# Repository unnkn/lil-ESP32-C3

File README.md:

<!-- PROJECT LOGO -->
<br />
<div align="center">

  <h3 align="center">Little ESP32 C3 Charger with wireless capabilities</h3>

  <p align="center">
    Here you can find all my project files.
    <br />
    <a href="https://github.com/Ans1S/lil-ESP32-C3"><strong>Explore the docs »</strong></a>
    <br />
    <br />
    <a href="https://github.com/Ans1S/lil-ESP32-C3/issues">Report Bug</a>
  </p>
</div>

## PCB Version 1: Advanced Wireless Communication and Power Management
<div align="center">

</div>

<div align="center">
  
</div>

<br />
<br />

The objective of this project is to develop a compact ESP32-C3 board with integrated Wi-Fi and Bluetooth capabilities. One of the standout features of this board is its ability to charge a LiPo battery (3.7V) while managing power distribution effectively. This is achieved through the inclusion of a sophisticated power path chip that seamlessly regulates both the charging of the battery and the power supply to the ESP32-C3 via USB.

#### Key Features:

1. **ESP32-C3 Integration**:
   - **Wi-Fi and Bluetooth**: The board leverages the ESP32-C3 microcontroller to provide robust wireless connectivity, supporting both Wi-Fi and Bluetooth communication.
   - **Compact Design**: Designed with a focus on miniaturization, making it suitable for a wide range of applications, from wearables to IoT devices.

2. **Power Management**:
   - **LiPo Battery Charging**: Capable of charging a 3.7V LiPo battery, ensuring your device remains powered even in the absence of a direct power source.
   - **Power Path Chip**: This chip plays a crucial role in managing the dual power sources (battery and USB). It allows for seamless switching between USB power and battery power, ensuring uninterrupted operation of the ESP32-C3.
   - **USB Power Regulation**: When connected to USB, the power path chip efficiently manages the power distribution, providing stable power to the ESP32-C3 while simultaneously charging the battery.

3. **Battery Management**:
   - **Monitoring and Control**: The ESP32-C3 is equipped with features to monitor and control the battery charging process. This includes the ability to track battery levels, regulate charging currents, and implement safety measures to prevent overcharging.
   - **Customizable Charging Profiles**: Through the ESP32-C3, users can customize the charging parameters to optimize for battery longevity and performance, adapting to different battery specifications and use cases.

#### Applications:

This versatile board is ideal for a variety of applications, including but not limited to:
- **IoT Devices**: Providing reliable connectivity and power management for smart home devices, sensors, and other IoT solutions.
- **Wearable Technology**: Offering a compact and efficient solution for wearable tech, ensuring extended battery life and connectivity.
- **Portable Electronics**: Suitable for portable gadgets that require stable wireless communication and efficient power management.

In summary, this project aims to deliver a powerful, compact, and versatile ESP32-C3 board that excels in wireless communication and advanced power management, making it an excellent choice for modern electronic applications.

<p align="right">(<a href="#readme-top">back to top</a>)</p>

## New Chapter: Second Version of the Board

<div align="center">

</div>

### Introduction
The second version of our ESP32-C3 board is currently under development and introduces several significant enhancements to improve functionality, power management, and overall performance. This chapter outlines the key improvements and new features of the updated board.

### Key Improvements and Features

1. **I2C Connector**
   - **New Addition**: An I2C connector has been integrated into the board, facilitating easy connection of various I2C peripherals, such as sensors and displays.
   - **Benefits**: This addition simplifies the expansion of the board’s capabilities and makes it more versatile for different applications.

2. **Battery Protection Circuit**
   - **Enhanced Safety**: A dedicated protection circuit for the battery has been included to prevent overcharging, deep discharge, and short circuits.
   - **Advantages**: This ensures the longevity and safety of the battery, making the board more reliable for long-term use.

3. **New Charging IC**
   - **Upgraded Charging IC**: The new charging IC supports a 5V output, enhancing the efficiency of battery charging and power management.
   - **Improved Performance**: This upgrade ensures stable and efficient power delivery, especially important when the board is powered through USB while simultaneously charging the battery.

4. **Low Dropout Regulator (LDO)**
   - **Voltage Regulation**: A new LDO has been added to step down the 5V to 3.3V, which is necessary for powering the ESP32-C3.
   - **Consistent Operation**: This allows the ESP32-C3 to operate consistently even when the battery is at a low charge, ensuring uninterrupted performance.

5. **Battery Level Monitoring**
   - **Feature Addition**: The capability to read the battery’s charge level has been implemented.
   - **User Benefit**: This feature allows users to monitor the battery status in real-time, enabling better power management and timely recharging.

6. **Transition to a 4-Layer PCB**
   - **Design Upgrade**: The board design has been upgraded from a 2-layer PCB to a 4-layer PCB.
   - **Enhanced Performance**: This transition improves signal integrity, reduces electromagnetic interference (EMI), and enhances the overall robustness of the board. It also allows for more efficient layout of components, contributing to better performance and reliability.

### Conclusion
The second version of the ESP32-C3 board brings significant enhancements in power management, safety, and expandability. These improvements ensure that the board remains at the forefront of compact and efficient design, suitable for a wide range of applications from IoT devices to portable electronics. With the integration of new components and a more sophisticated PCB design, the board is poised to deliver even better performance and reliability in various use cases.

<p align="right">(<a href="#readme-top">back to top</a>)</p>

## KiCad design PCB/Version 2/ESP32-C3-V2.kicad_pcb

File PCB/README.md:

# lil-ESP32-C3
 Ein möglichst kleines WIFI Board

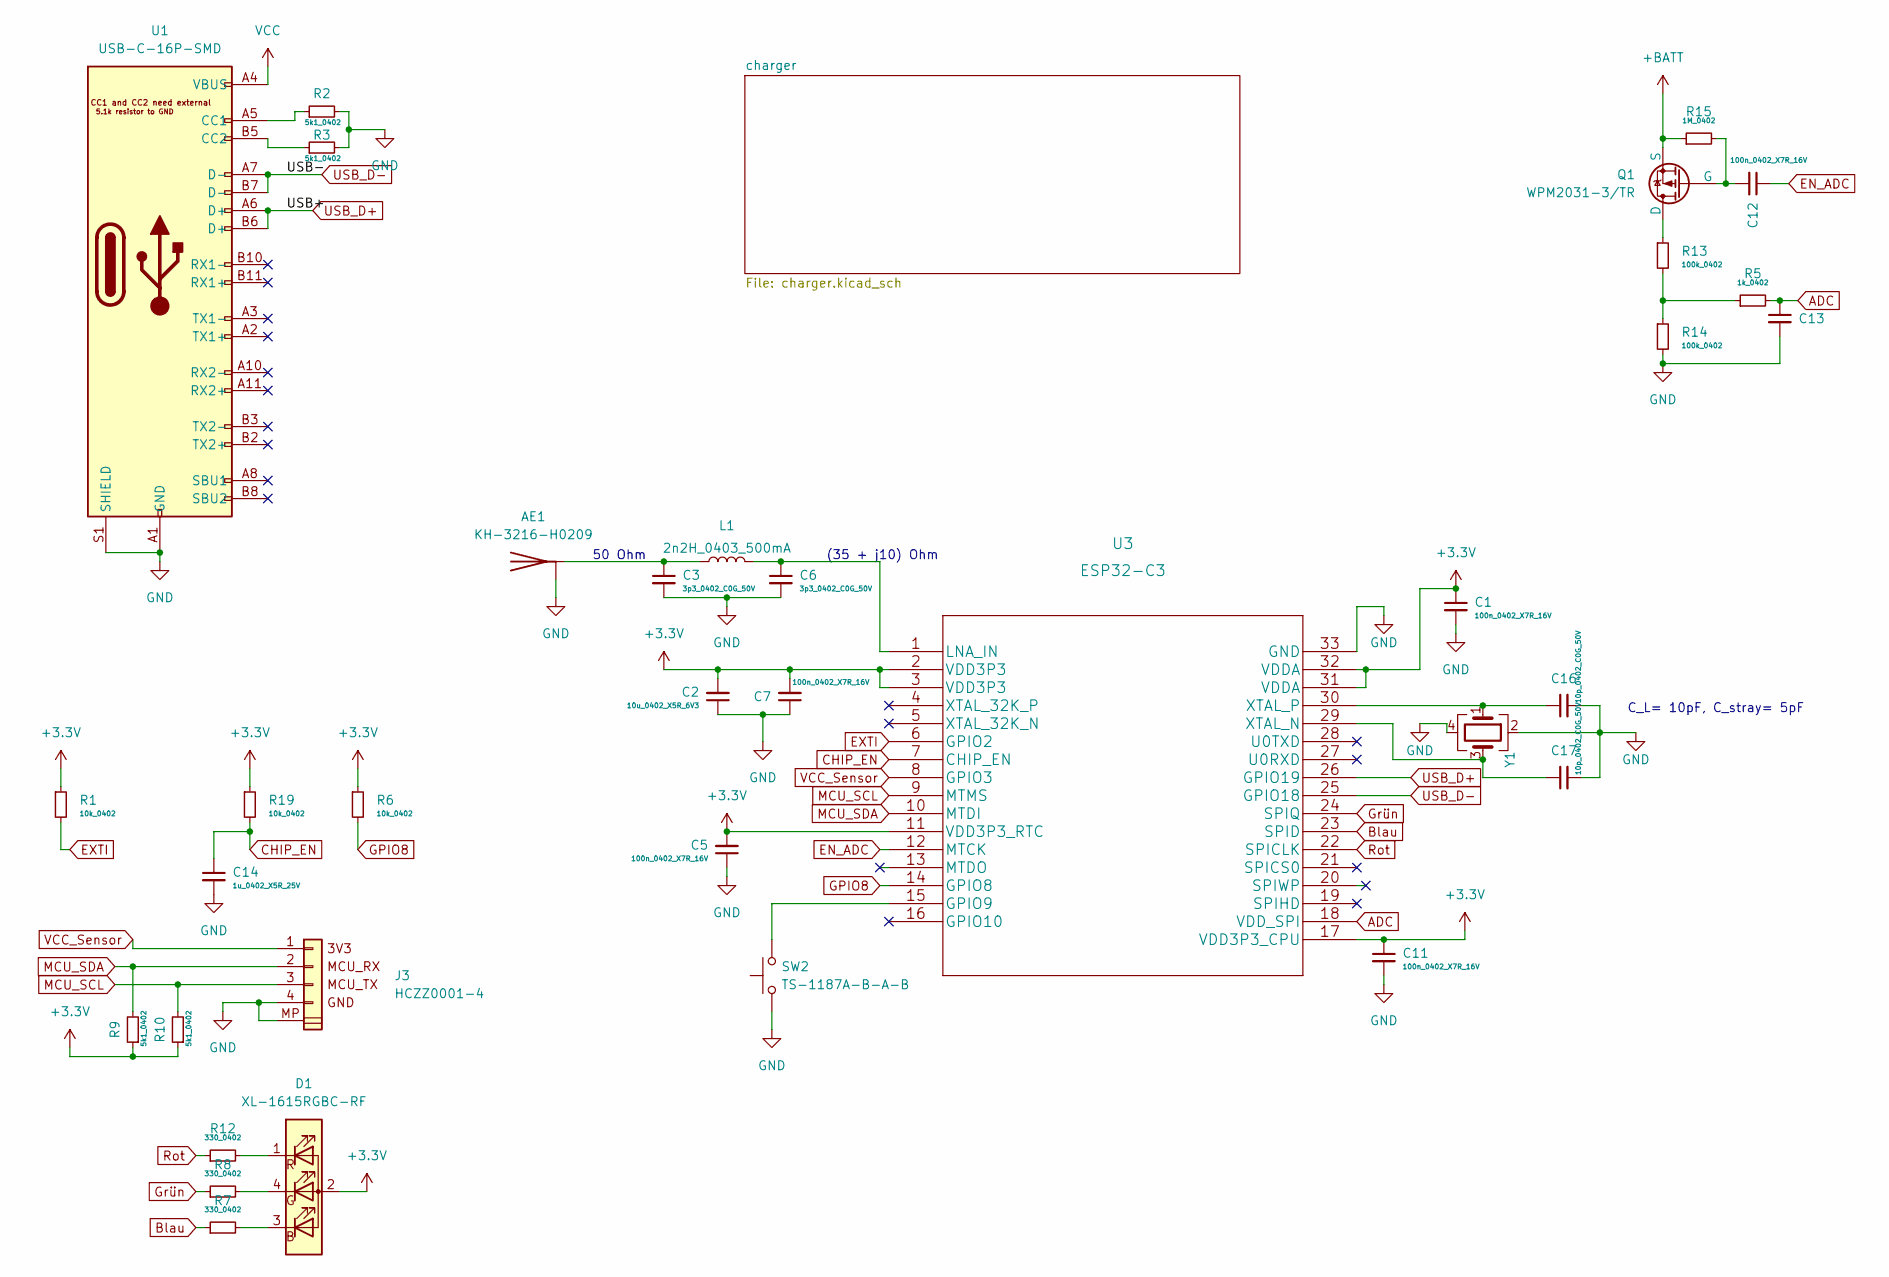
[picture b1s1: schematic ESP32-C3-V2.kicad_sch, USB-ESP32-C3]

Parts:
AE1: KH-3216-H0209; Texas_SWRA117D_2.4GHz_Left; LCSC C2925417
C1, C5, C7, C11, C12, C13: 100n_0402_X7R_16V; C_0402_1005Metric; LCSC C1525
C2: 10u_0402_X5R_6V3; C_0402_1005Metric; LCSC C15525
C3, C6: 3p3_0402_C0G_50V; C_0402_1005Metric; LCSC C1565
C14: 1u_0402_X5R_25V; C_0402_1005Metric; LCSC C52923
C16, C17: 10p_0402_C0G_50V; C_0402_1005Metric; LCSC C1634
D1: XL-1615RGBC-RF; LED_0606_1432_correct; LCSC C965840
J3: HCZZ0001-4; JST_GH_SM04B-GHS-TB_1x04-1MP_P1.25mm_Horizontal; LCSC C7433455
L1: 2n2H_0403_500mA; R_0402_1005Metric; LCSC C76790
Q1: WPM2031-3/TR; SOT-723; LCSC C240201
R1, R6, R19: 10k_0402; R_0402_1005Metric; Voltage 50V; LCSC C25744
R2, R3, R9, R10: 5k1_0402; R_0402_1005Metric; Voltage 50V; LCSC C25905
R5: 1k_0402; R_0402_1005Metric; Voltage 50V; LCSC C11702
R7, R8, R12: 330_0402; R_0402_1005Metric; Voltage 50V; LCSC C25104
R13, R14: 100k_0402; R_0402_1005Metric; Voltage 50V; LCSC C25741
R15: 1M_0402; R_0402_1005Metric; Voltage 50V; LCSC C26083
SW2: TS-1187A-B-A-B; SW_SPST_TL3305B; LCSC C318884
U1: USB-C-16P-SMD; USB-C-MC-311D; Partnumber SOFNG MC-311D; LCSC C136423
U3: ESP32-C3; QFN-32-1EP_5x5mm_P0.5mm_EP3.7x3.7mm; LCSC C2858491
Y1: 40MHz_S3240000151040; Crystal_SMD_3225-4Pin_3.2x2.5mm; LCSC C5261247

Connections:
+3.3V: C1.1, C2.2, C5.2, C7.2, C11.1, D1.2 (A), R1.1, R6.1, R9.1, R10.1, R19.1, U3.2 (VDD3P3), U3.3 (VDD3P3), U3.11 (VDD3P3_RTC), U3.17 (VDD3P3_CPU), U3.31 (VDDA), U3.32 (VDDA); also elsewhere on the board
+BATT: Q1.2 (S), R15.1; also elsewhere on the board
ADC: C13.1, R5.2, U3.18 (VDD_SPI)
Blau: R7.1, U3.23 (SPID)
CHIP_EN: C14.1, R19.2, U3.7 (CHIP_EN)
EN_ADC: C12.1, U3.12 (MTCK)
EXTI: R1.2, U3.6 (GPIO2)
GND: AE1.2 (GND), C1.2, C2.1, C3.2, C5.1, C6.2, C7.1, C11.2, C13.2, C14.2, C16.2, C17.2, J3.4, J3.MP, R2.2, R3.2, R14.2, SW2.1, U1.A1 (GND), U1.A12 (GND), U1.B1 (GND), U1.B12 (GND), U1.S1 (SHIELD), U3.33 (GND), Y1.2 (GND), Y1.4 (GND); also elsewhere on the board
GPIO8: R6.2, U3.14 (GPIO8)
Grün: R8.1, U3.24 (SPIQ)
MCU_SCL: J3.3, R10.2, U3.9 (MTMS)
MCU_SDA: J3.2, R9.2, U3.10 (MTDI)
unnamed: AE1.1 (A), C3.1, L1.1
unnamed: D1.3 (BK), R7.2
unnamed: D1.4 (GK), R8.2
unnamed: D1.1 (RK), R12.2
unnamed: Q1.3 (D), R13.1
unnamed: C12.2, Q1.1 (G), R15.2
unnamed: R5.1, R13.2, R14.1
unnamed: R2.1, U1.A5 (CC1)
unnamed: R3.1, U1.B5 (CC2)
unnamed: SW2.2, U3.15 (GPIO9)
unnamed: C6.1, L1.2, U3.1 (LNA_IN)
unnamed: C17.1, U3.29 (XTAL_N), Y1.3 (OSC2)
unnamed: C16.1, U3.30 (XTAL_P), Y1.1 (OSC1)
Rot: R12.1, U3.22 (SPICLK)
USB_D+: U1.A6 (D+), U1.B6 (D+), U3.26 (GPIO19)
USB_D-: U1.A7 (D-), U1.B7 (D-), U3.25 (GPIO18)
VCC: U1.A4 (VBUS), U1.A9 (VBUS), U1.B4 (VBUS), U1.B9 (VBUS); also elsewhere on the board
VCC_Sensor: J3.1, U3.8 (GPIO3)

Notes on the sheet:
50 Ohm
(35 + j10) Ohm
C_L= 10pF, C_stray= 5pF

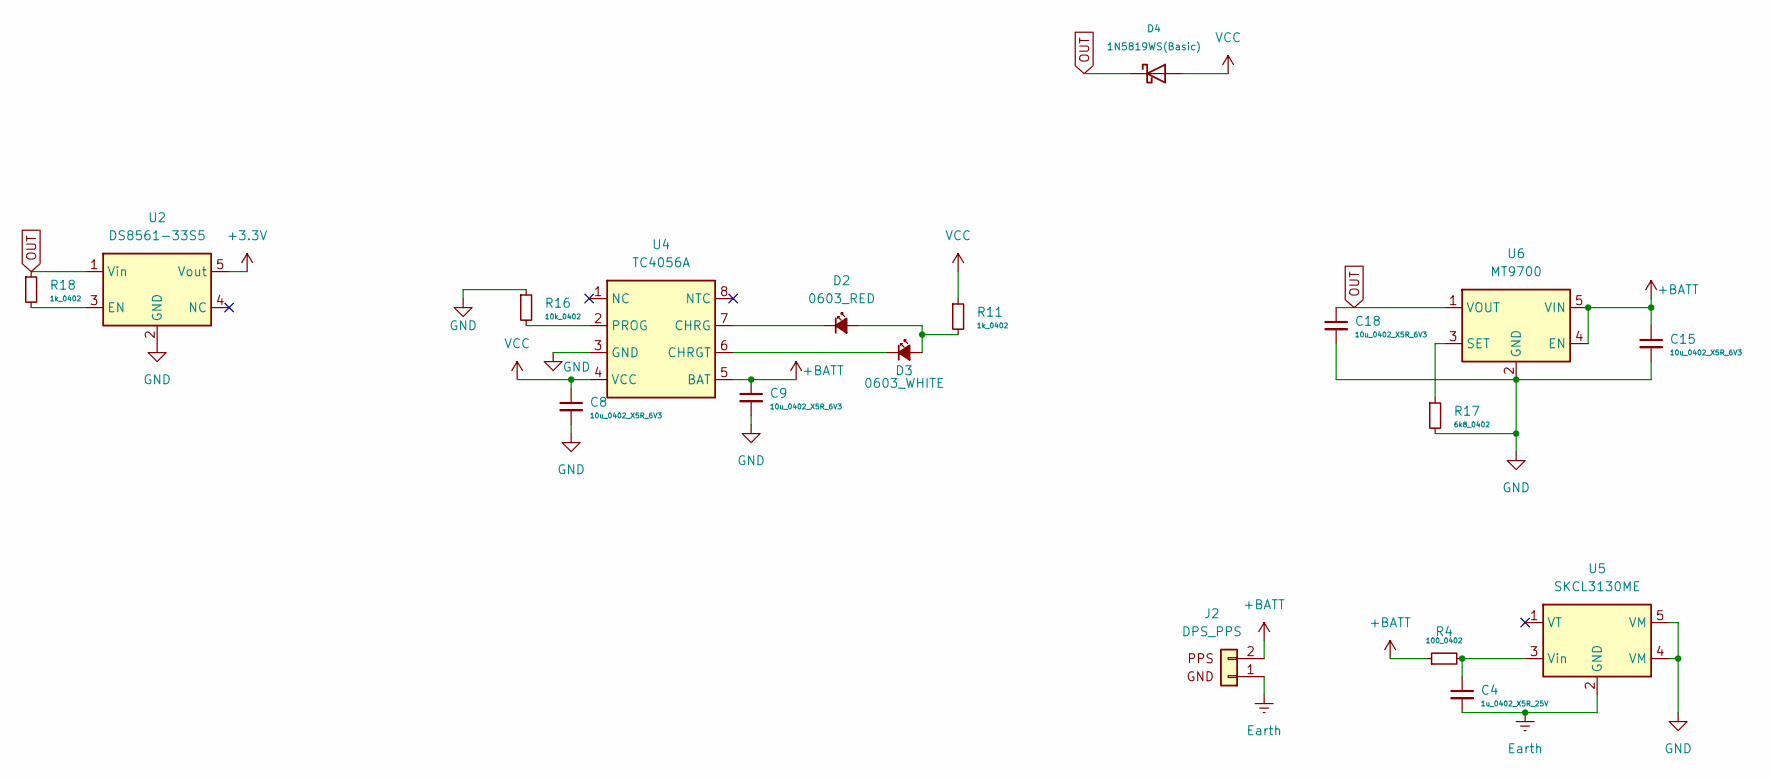
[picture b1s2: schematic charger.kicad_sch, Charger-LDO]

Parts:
C4: 1u_0402_X5R_25V; C_0402_1005Metric; LCSC C52923
C8, C9, C15, C18: 10u_0402_X5R_6V3; C_0402_1005Metric; LCSC C15525
D2: 0603_RED; LED_0603_1608Metric; Partnumber KT-0603R; LCSC C2286
D3: 0603_WHITE; LED_0603_1608Metric; Partnumber 19-217/GHC-YR1S2/3T; LCSC C2290
D4: 1N5819WS(Basic); D_SOD-323_HandSoldering; LCSC C191023
J2: DPS_PPS; JST_PH_B2B-PH-K_1x02_P2.00mm_Vertical; LCSC C722767
R4: 100_0402; R_0402_1005Metric; Voltage 50V; LCSC C25076
R11, R18: 1k_0402; R_0402_1005Metric; Voltage 50V; LCSC C11702
R16: 10k_0402; R_0402_1005Metric; Voltage 50V; LCSC C25744
R17: 6k8_0402; R_0402_1005Metric; Voltage 50V; LCSC C25917
U2: DS8561-33S5; SOT-23-5; LCSC C5795637
U4: TC4056A; SOP-8_3.9x4.9mm_P1.27mm; LCSC C7588528
U5: SKCL3130ME; SOT-23-5; LCSC C2941741
U6: MT9700; SOT-23-5; LCSC C89855

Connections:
+3.3V: U2.5 (Vout); also elsewhere on the board
+BATT: C9.1, C15.1, J2.2, R4.1, U4.5 (BAT), U6.4 (EN), U6.5 (VIN); also elsewhere on the board
Earth: C4.2, J2.1, U5.2 (GND)
GND: C8.2, C9.2, C15.2, C18.2, R16.1, R17.2, U2.2 (GND), U4.3 (GND), U5.4 (VM), U5.5 (VM), U6.2 (GND); also elsewhere on the board
unnamed: D2.2 (A), D3.2 (A), R11.2
unnamed: D2.1 (K), U4.7 (CHRG)
unnamed: D3.1 (K), U4.6 (CHRGT)
unnamed: R18.2, U2.3 (EN)
unnamed: R16.2, U4.2 (PROG)
unnamed: C4.1, R4.2, U5.3 (Vin)
unnamed: R17.1, U6.3 (SET)
OUT: C18.1, D4.1 (K), R18.1, U2.1 (Vin), U6.1 (VOUT)
VCC: C8.1, D4.2 (A), R11.1, U4.4 (VCC); also elsewhere on the board

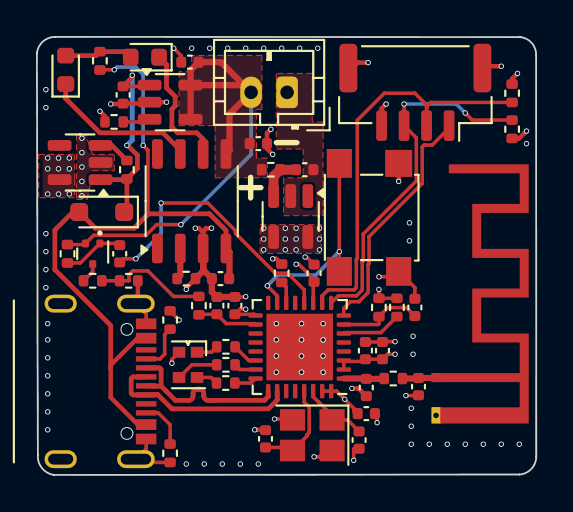
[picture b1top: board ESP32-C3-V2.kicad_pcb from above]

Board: 4 copper layers, 27.7 x 24.3 mm, 53 parts (0 on the bottom side), 39 nets.

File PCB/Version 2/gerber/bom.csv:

Comment,Designator,Footprint,LCSC
10p_0402_C0G_50V,"C16,C17",Capacitor_SMD:C_0402_1005Metric,C1634
10k_0402,"R1,R6,R19,R20",Resistor_SMD:R_0402_1005Metric,C25744
5k1_0402,"R2,R3,R9,R10,R16",Resistor_SMD:R_0402_1005Metric,C25905
10u_0402_X5R_6V3,C2,Capacitor_SMD:C_0402_1005Metric,C15525
1k_0402,"R5,R18",Resistor_SMD:R_0402_1005Metric,C11702
1M_0402,R15,Resistor_SMD:R_0402_1005Metric,C26083
330_0402,"R7,R8,R12",Resistor_SMD:R_0402_1005Metric,C25104
100n_0402_X7R_16V,"C1,C5,C7,C11,C12,C13",Capacitor_SMD:C_0402_1005Metric,C1525
2n2H_0403_500mA,L1,Resistor_SMD:R_0402_1005Metric,C76790
100k_0402,"R13,R14",Resistor_SMD:R_0402_1005Metric,C25741
1u_0402_X5R_25V,"C4,C8,C14",Capacitor_SMD:C_0402_1005Metric,C52923
3p3_0402_C0G_50V,"C3,C6",Capacitor_SMD:C_0402_1005Metric,C1565
HCZZ0001-4,J3,Connector_JST:JST_GH_SM04B-GHS-TB_1x04-1MP_P1.25mm_Horizontal,C7433455
40MHz_S3240000151040,Y1,Crystal:Crystal_SMD_3225-4Pin_3.2x2.5mm,C5261247
WPM2031-3/TR ,Q1,Package_TO_SOT_SMD:SOT-723,C240201
TS-1187A-B-A-B,SW2,switch:SW_SPST_TL3305B,C318884 
XL-1615RGBC-RF,D1,LEDSMD:LED_0606_1432_correct,C965840
USB-C-16P-SMD,U1,DPSConnector:USB-C-MC-311D,C136423
ESP32-C3,U3,Package_DFN_QFN:QFN-32-1EP_5x5mm_P0.5mm_EP3.7x3.7mm,C2858491
0603_RED,D2,LED_SMD:LED_0603_1608Metric,C2286
SKCL3130ME,U5,Package_TO_SOT_SMD:SOT-23-5,C2941741 
4u7_0402_X5R _10V,"C9,C10",Capacitor_SMD:C_0402_1005Metric,C23733
DS8561-33S5 ,U2,Package_TO_SOT_SMD:SOT-23-5,C5795637
1k5_0603,R11,Resistor_SMD:R_0603_1608Metric,C22843
0603_WHITE,D3,LED_SMD:LED_0603_1608Metric,C2290
3k_0402,"R17,R21",Resistor_SMD:R_0402_1005Metric,C25890
DPS_PPS,J2,Connector_JST:JST_PH_B2B-PH-K_1x02_P2.00mm_Vertical,C722767
BQ24073RGTR,U4,Package_DFN_QFN:VQFN-16-1EP_3x3mm_P0.5mm_EP1.6x1.6mm,C15220
100_0402,R4,Resistor_SMD:R_0402_1005Metric,C25076

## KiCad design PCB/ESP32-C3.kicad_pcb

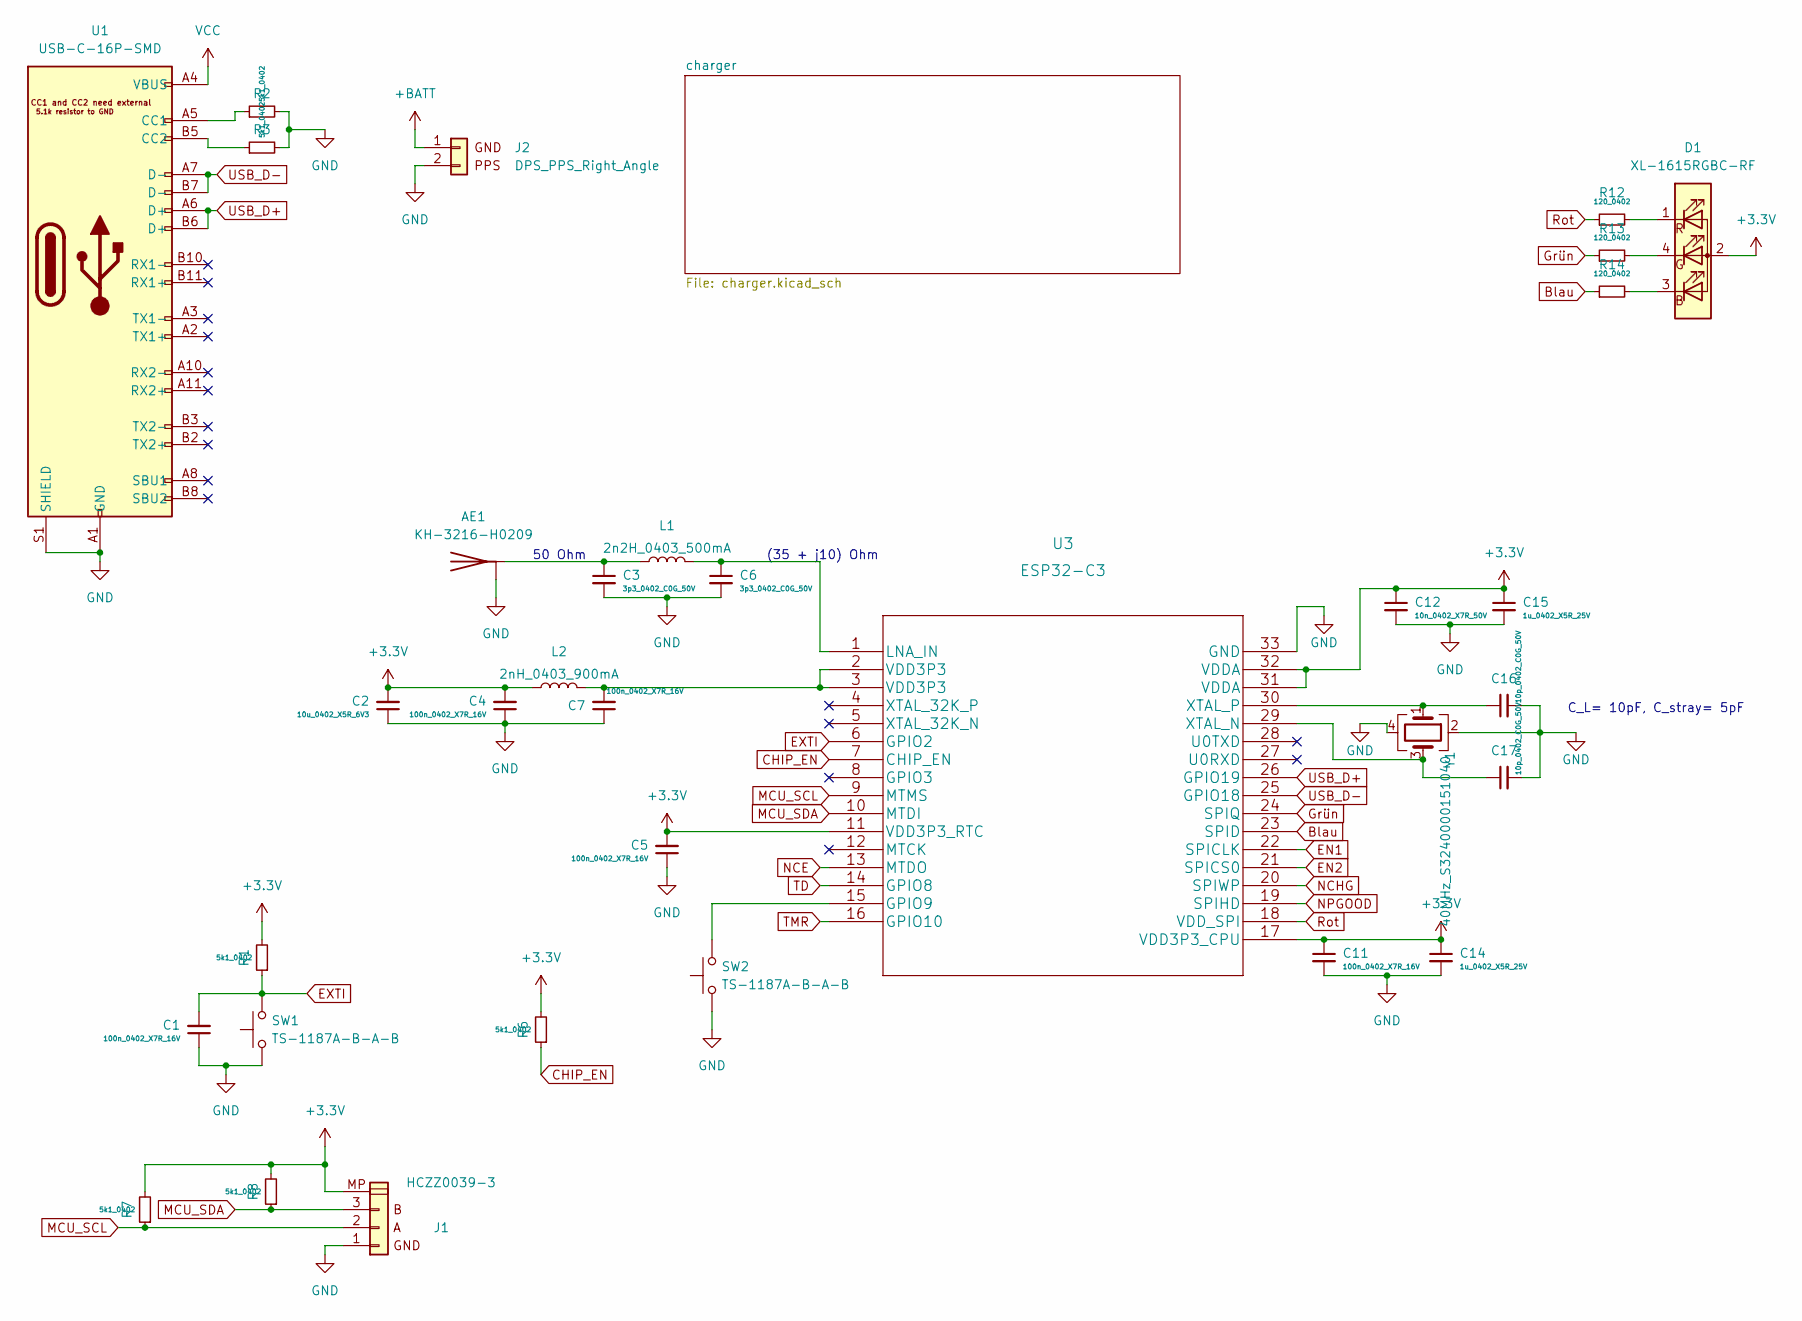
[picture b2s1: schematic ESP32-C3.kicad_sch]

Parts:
AE1: KH-3216-H0209; Texas_SWRA117D_2.4GHz_Left; LCSC C2925417
C1, C4, C5, C7, C11: 100n_0402_X7R_16V; C_0402_1005Metric; LCSC C1525
C2: 10u_0402_X5R_6V3; C_0402_1005Metric; LCSC C15525
C3, C6: 3p3_0402_C0G_50V; C_0402_1005Metric; LCSC C1565
C12: 10n_0402_X7R_50V; C_0402_1005Metric; LCSC C15195
C14, C15: 1u_0402_X5R_25V; C_0402_1005Metric; LCSC C52923
C16, C17: 10p_0402_C0G_50V; C_0402_1005Metric; LCSC C1634
D1: XL-1615RGBC-RF; LED_0606_1432; LCSC C965840
J1: HCZZ0039-3; JST_SH_SM03B-SRSS-TB_1x03-1MP_P1.00mm_Horizontal; LCSC C7433424
J2: DPS_PPS_Right_Angle; JST_PH_S2B-PH-K_1x02_P2.00mm_Horizontal; LCSC C7465576
L1: 2n2H_0403_500mA; R_0402_1005Metric; LCSC C76790
L2: 2nH_0403_900mA; R_0402_1005Metric; LCSC C18216
R1, R2, R3, R6, R7, R8: 5k1_0402; R_0402_1005Metric; Voltage 50V; LCSC C25905
R12, R13, R14: 120_0402; R_0402_1005Metric; Voltage 50V; LCSC C25079
SW1, SW2: TS-1187A-B-A-B; SW_SPST_TL3305B; LCSC C318884
U1: USB-C-16P-SMD; USB-C-MC-311D; Partnumber SOFNG MC-311D; LCSC C136423
U3: ESP32-C3; QFN-32-1EP_5x5mm_P0.5mm_EP3.7x3.7mm; LCSC C2858491
Y1: 40MHz_S3240000151040; Crystal_SMD_3225-4Pin_3.2x2.5mm; LCSC C5261247

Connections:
+3.3V: C2.2, C4.2, C5.2, C11.1, C12.1, C14.1, C15.1, D1.2 (A), J1.MP, L2.1, R1.2, R6.2, R7.2, R8.2, U3.11 (VDD3P3_RTC), U3.17 (VDD3P3_CPU), U3.31 (VDDA), U3.32 (VDDA); also elsewhere on the board
+BATT: J2.1; also elsewhere on the board
Blau: R14.1, U3.23 (SPID)
CHIP_EN: R6.1, U3.7 (CHIP_EN)
EN1: U3.22 (SPICLK); also elsewhere on the board
EN2: U3.21 (SPICS0); also elsewhere on the board
EXTI: C1.2, R1.1, SW1.2, U3.6 (GPIO2)
GND: AE1.2 (GND), C1.1, C2.1, C3.2, C4.1, C5.1, C6.2, C7.1, C11.2, C12.2, C14.2, C15.2, C16.2, C17.2, J1.1, J2.2, R2.2, R3.2, SW1.1, SW2.1, U1.A1 (GND), U1.A12 (GND), U1.B1 (GND), U1.B12 (GND), U1.S1 (SHIELD), U3.33 (GND), Y1.2 (GND), Y1.4 (GND); also elsewhere on the board
Grün: R13.1, U3.24 (SPIQ)
MCU_SCL: J1.2, R7.1, U3.9 (MTMS)
MCU_SDA: J1.3, R8.1, U3.10 (MTDI)
NCE: U3.13 (MTDO); also elsewhere on the board
NCHG: U3.20 (SPIWP); also elsewhere on the board
NPGOOD: U3.19 (SPIHD); also elsewhere on the board
unnamed: AE1.1 (A), C3.1, L1.1
unnamed: C7.2, L2.2, U3.2 (VDD3P3), U3.3 (VDD3P3)
unnamed: D1.3 (BK), R14.2
unnamed: D1.4 (GK), R13.2
unnamed: D1.1 (RK), R12.2
unnamed: R2.1, U1.A5 (CC1)
unnamed: R3.1, U1.B5 (CC2)
unnamed: SW2.2, U3.15 (GPIO9)
unnamed: C6.1, L1.2, U3.1 (LNA_IN)
unnamed: C17.1, U3.29 (XTAL_N), Y1.3 (OSC2)
unnamed: C16.1, U3.30 (XTAL_P), Y1.1 (OSC1)
Rot: R12.1, U3.18 (VDD_SPI)
TD: U3.14 (GPIO8); also elsewhere on the board
TMR: U3.16 (GPIO10); also elsewhere on the board
USB_D+: U1.A6 (D+), U1.B6 (D+), U3.26 (GPIO19)
USB_D-: U1.A7 (D-), U1.B7 (D-), U3.25 (GPIO18)
VCC: U1.A4 (VBUS), U1.A9 (VBUS), U1.B4 (VBUS), U1.B9 (VBUS); also elsewhere on the board

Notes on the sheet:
50 Ohm
(35 + j10) Ohm
C_L= 10pF, C_stray= 5pF

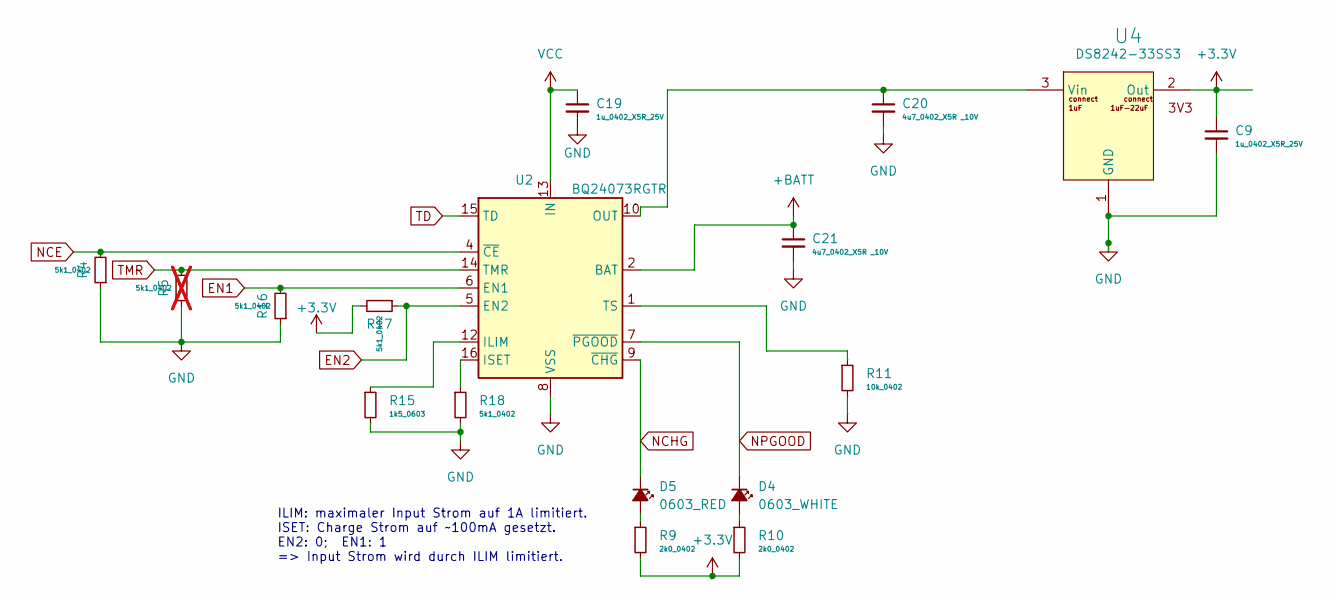
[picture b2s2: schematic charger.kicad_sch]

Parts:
C9, C19: 1u_0402_X5R_25V; C_0402_1005Metric; LCSC C52923
C20, C21: 4u7_0402_X5R _10V; C_0402_1005Metric; LCSC C23733
D4: 0603_WHITE; LED_0603_1608Metric; Partnumber 19-217/GHC-YR1S2/3T; LCSC C2290
D5: 0603_RED; LED_0603_1608Metric; Partnumber KT-0603R; LCSC C2286
R4, R16, R17: 5k1_0402; R_0402_1005Metric; Voltage 50V; LCSC C25905
R5: 5k1_0402; R_0402_1005Metric; Voltage 50V; LCSC C25905; not fitted
R9, R10: 2k0_0402; R_0402_1005Metric; Voltage 50V; LCSC C4109
R11: 10k_0402; R_0402_1005Metric; Voltage 50V; LCSC C25744
R15: 1k5_0603; R_0603_1608Metric; Voltage 75V; LCSC C22843
R18: 5k1_0402; R_0402_1005Metric; LCSC C25905
U2: BQ24073RGTR; VQFN-16-1EP_3x3mm_P0.5mm_EP1.6x1.6mm; LCSC C15220
U4: DS8242-33SS3; SOT-23; LCSC C5884134

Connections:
+3.3V: C9.1, R9.2, R10.2, R17.2, U4.2 (Out); also elsewhere on the board
+BATT: C21.1, U2.2 (BAT), U2.3 (BAT); also elsewhere on the board
EN1: R16.2, U2.6 (EN1); also elsewhere on the board
EN2: R17.1, U2.5 (EN2); also elsewhere on the board
GND: C9.2, C19.2, C20.2, C21.2, R4.1, R5.1, R11.2, R15.2, R16.1, R18.2, U2.8 (VSS), U2.17 (VSS), U4.1 (GND); also elsewhere on the board
NCE: R4.2, U2.4 (~CE); also elsewhere on the board
NCHG: D5.1 (K), U2.9 (~CHG); also elsewhere on the board
NPGOOD: D4.1 (K), U2.7 (~PGOOD); also elsewhere on the board
unnamed: D4.2 (A), R10.1
unnamed: D5.2 (A), R9.1
unnamed: R15.1, U2.12 (ILIM)
unnamed: R18.1, U2.16 (ISET)
unnamed: R11.1, U2.1 (TS)
unnamed 30: C20.1, U2.10 (OUT), U2.11 (OUT), U4.3 (Vin); also elsewhere on the board
TD: U2.15 (TD); also elsewhere on the board
TMR: R5.2, U2.14 (TMR); also elsewhere on the board
VCC: C19.1, U2.13 (IN); also elsewhere on the board

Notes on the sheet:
ILIM: maximaler Input Strom auf 1A limitiert. ISET: Charge Strom auf ~100mA gesetzt. EN2: 0; EN1: 1 => Input Strom wird durch ILIM limitiert.

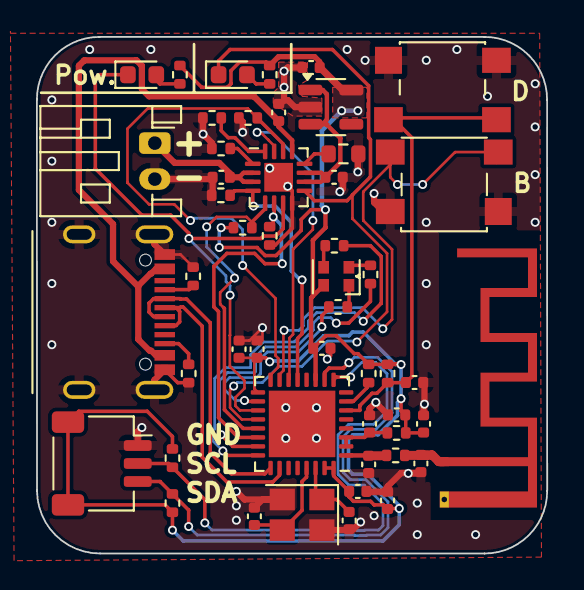
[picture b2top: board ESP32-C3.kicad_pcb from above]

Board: 2 copper layers, 28.3 x 28.7 mm, 50 parts (0 on the bottom side), 37 nets.

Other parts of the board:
U5: WL9003S5-33; SOT-23-5

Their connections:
+3.3V: U5.5 (Out); also elsewhere on the board
GND: U5.2 (GND); also elsewhere on the board
unnamed 30: U5.1 (Vin), U5.3 (EN); also elsewhere on the board

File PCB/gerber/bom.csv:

Comment,Designator,Footprint,LCSC
10p_0402_C0G_50V,"C16,C17",Capacitor_SMD:C_0402_1005Metric,C1634
100n_0402_X7R_16V,"C1,C4,C5,C7,C11",Capacitor_SMD:C_0402_1005Metric,C1525
10u_0402_X5R_6V3,C2,Capacitor_SMD:C_0402_1005Metric,C15525
5k1_0402,"R1,R2,R3,R4,R6,R7,R8,R16,R17,R18",Resistor_SMD:R_0402_1005Metric,C25905
1u_0402_X5R_25V,"C14,C15,C19",Capacitor_SMD:C_0402_1005Metric,C52923
2nH_0403_900mA,L2,Resistor_SMD:R_0402_1005Metric,C18216
2n2H_0403_500mA,L1,Resistor_SMD:R_0402_1005Metric,C76790
100_0402,"R14,R19,R21",Resistor_SMD:R_0402_1005Metric,C25076
TS-1187A-B-A-B,"SW1,SW2",switch:SW_SPST_TL3305B,C318884 
DPS_PPS_Right_Angle,J2,Connector_JST:JST_PH_S2B-PH-K_1x02_P2.00mm_Horizontal,C7465576
3p3_0402_C0G_50V,"C3,C6",Capacitor_SMD:C_0402_1005Metric,C1565
40MHz_S3240000151040,Y1,Crystal:Crystal_SMD_3225-4Pin_3.2x2.5mm,C5261247
HCZZ0039-3,J1,Connector_JST:JST_SH_SM03B-SRSS-TB_1x03-1MP_P1.00mm_Horizontal,C7433424
10n_0402_X7R_50V,C12,Capacitor_SMD:C_0402_1005Metric,C15195
XL-1615RGBC-RF,D1,LEDSMD:LED_0606_1432,C965840
USB-C-16P-SMD,U1,DPSConnector:USB-C-MC-311D,C136423
ESP32-C3,U3,Package_DFN_QFN:QFN-32-1EP_5x5mm_P0.5mm_EP3.7x3.7mm,C2858491
0603_RED,D5,LED_SMD:LED_0603_1608Metric,C2286
4u7_0402_X5R _10V,"C20,C21",Capacitor_SMD:C_0402_1005Metric,C23733
2k0_0402,"R9,R10",Resistor_SMD:R_0402_1005Metric,C4109
1k5_0603,R15,Resistor_SMD:R_0603_1608Metric,C22843
0603_WHITE,D4,LED_SMD:LED_0603_1608Metric,C2290
10k_0402,R11,Resistor_SMD:R_0402_1005Metric,C25744
BQ24072RGT,U2,Package_DFN_QFN:VQFN-16-1EP_3x3mm_P0.5mm_EP1.6x1.6mm,C140288

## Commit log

2023-02-01 gerber erstellt
2023-07-24 update to KiCad 7
2023-08-23 save
2024-01-26 updated the charging circuit
2024-01-27 Mit dem Layout angefangen
2024-02-02 Layout weiter gemacht.
2024-05-24 Zur Kontrolle fertig.
2024-05-26 Neuste Version
2024-05-30 Boot Button hinzugefügt
2024-05-30 Wichtige Änderungen für die Fertigung
2024-06-02 Kleine Verbesserungen
2024-06-04 SW entfernt
2024-06-05 kleiner Versuch
2024-06-05 Neuer Charger IC und ein LDO
2024-06-06 LDO hinzugefügt
2024-06-07 README
2024-06-11 neues Bild
2024-06-14 back up
2024-06-15 Started with version 2 of the PCB and added a Lib with all the new components
2024-06-15 changed the JST Connector to a 4 Pin
2024-06-22 Working on Version 2
2024-06-24 Version 2
2024-06-25 V2 für Kontrolle fertig
2024-06-25 Schaltplan in als PDF
2024-06-26 neue Bilder, Gerber, PDF
2024-06-28 backup
2024-07-01 new picture
2024-07-03 Version 2 zur Korrektur fertig
2024-07-04 Platine geprüft und überarbeitet
